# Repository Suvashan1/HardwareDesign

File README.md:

# STM32 Breakout-Board using STM32F103C8T6 Microcontroller

Using this medium-density microcontroller, an experimental peripheral board was designed using KiCAD to validate PCB design principles that I have learnt. It has formed a template for future layouts and schematic designs. For further information on my design choices, method and components selected and their placement, please read the design-considerations PDF in the file.

# Layout:

# Schematic:

# BOSCH BMP180 Drivers

The following device drivers were developed to be used with the respective breakout board designed, to test the I2C interface. All instructions and files can be found in the folder
added.

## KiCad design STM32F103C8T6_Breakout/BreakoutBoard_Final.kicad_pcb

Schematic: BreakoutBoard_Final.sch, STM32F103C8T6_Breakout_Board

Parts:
C1, C3: 12p; C_0805_2012Metric; LCSC Part # C1792
C2: 10u; C_1206_3216Metric; LCSC Part # C13585
C4: 10u; C_0805_2012Metric; LCSC Part # C15850
C5: 10u; C_0402_1005Metric; LCSC Part # C15525
C6, C8, C10, C11, C12, C13, C14, C16, C17, C18: 100n; C_0402_1005Metric; LCSC Part # C1525
C7, C9: 22p; C_0805_2012Metric; LCSC Part # C1804
C15: 1u; C_0603_1608Metric; LCSC Part # C15849
D1, D2: B5819W; D_SOD-123; LCSC Part # C8598
D3: Status; LED_0603_1608Metric; LCSC Part # C72041
J1: USB_B_Micro; USB_Micro-B_Molex-105017-0001
J2: SWD; PinHeader_2x05_P1.00mm_Vertical
J3: BMP180_I2C; PinSocket_1x04_P1.00mm_Vertical
J4: SPI_F; PinSocket_1x04_P1.00mm_Vertical
J5: USART_F; PinSocket_1x02_P1.00mm_Vertical
J6: SPI_M; PinHeader_1x04_P1.00mm_Vertical
J7: USART_M; PinHeader_1x02_P1.00mm_Vertical
J8: HC-05; PinSocket_1x04_P1.00mm_Vertical
J9: VCC_GND; PinHeader_1x02_P1.00mm_Vertical
J10: 3V3_GND; PinHeader_1x02_P1.00mm_Vertical
J11: 5V_GND; PinHeader_1x02_P1.00mm_Vertical
L1: Ferrite_Bead_Small; L_0805_2012Metric; LCSC Part # C1017
MH1, MH2, MH3, MH4: MountingHole_Pad; MountingHole_4.3mm_M4_Pad_Via
R1: 390; R_0805_2012Metric; LCSC Part # C17655
R2: 33ohm; R_0805_2012Metric; LCSC Part # C17634
R3, R4: 4.7k; R_1206_3216Metric; LCSC Part # C17936
R6, R8, R9, R10, R11: 1k; R_0402_1005Metric; LCSC Part # C11702
R7: 2.2k; R_0402_1005Metric; LCSC Part # C25879
R12: 1.5k; R_0201_0603Metric; LCSC Part # C22483
SW1: BOOT0_BOOT1; SW_DIP_SPSTx02_Slide_6.7x6.64mm_W7.62mm_P2.54mm_LowProfile
SW3: SW_Push_Dual; SW_PUSH_6mm
U1: USBLC6-2SC6; SOT-23-6; LCSC Part # C7519
U2: NCP1117; SOT-223-3_TabPin2; LCSC Part # C6186
U3: STM32F103C8Tx; LQFP-48_7x7mm_P0.5mm; LCSC Part # C8734
Y1: 16MHz; Crystal_SMD_3225-4Pin_3.2x2.5mm; LCSC Part # C13738
Y2: 32.768kHz; Crystal_SMD_3215-2Pin_3.2x1.5mm; LCSC Part # C32346

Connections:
+3.3VA: C14.1, C15.1, L1.1, U3.9
+3V3: C4.1, C5.1, C6.1, C8.1, C10.1, C11.1, C12.1, C16.1, C17.1, C18.1, J2.1, J3.4, J10.1, L1.2, R3.1, R4.1, R10.1, R11.1, R12.1, U2.2 (VO), U3.1, U3.24, U3.36, U3.48
+5V: D2.2, J1.1, J8.4, J11.1, U1.5
BOOT0: R8.1, SW1.1, U3.44
BOOT1: R9.1, SW1.2, U3.20
BT-RX: J8.1, R6.2, R7.2
BT-TX: J8.2, U3.22
GND: C1.2, C2.2, C3.2, C4.2, C5.2, C6.2, C7.2, C8.2, C9.2, C10.2, C11.2, C12.2, C13.1, C14.2, C15.2, C16.2, C17.2, C18.2, D3.1, J1.4, J1.5, J2.3, J2.5, J3.3, J8.3, J9.2, J10.2, J11.2, MH1.1, MH2.1, MH3.1, MH4.1, R7.1, R8.2, R9.2, SW3.2, U1.2, U2.1 (GND), U3.8, U3.23, U3.35, U3.47, Y1.2, Y1.4
HSE_IN: C1.1, U3.5, Y1.1
HSE_OUT: R1.1, U3.6
I2C_SCL: J3.2, R4.2, U3.42
I2C_SDA: J3.1, R3.2, U3.43
LSE_IN: C7.1, U3.3, Y2.1
LSE_OUT: C9.1, U3.4, Y2.2
NRST: C13.2, J2.10, SW3.1, U3.7
unnamed: C2.1, D1.1, D2.1, U2.3 (VI)
unnamed: C3.1, R1.2, Y1.3
unnamed: D3.2, R2.1
unnamed: R2.2, U3.18
unnamed: R10.2, SW1.4
unnamed: R11.2, SW1.3
SPI_MISO: J4.3, J6.2, U3.16
SPI_MOSI: J4.4, J6.1, U3.17
SPI_NSS: J4.1, J6.4, U3.14
SPI_SCK: J4.2, J6.3, U3.15
SWD_IO: J2.2, U3.34
SWO: J2.6, U3.39
SW_CLK: J2.4, U3.37
USART1_RX: J5.2, J7.2, U3.31
USART1_TX: J5.1, J7.1, U3.30
USART3_TX: R6.1, U3.21
USB_+: U1.4, U3.33
USB_-: U1.6, U3.32
USB_CONN+: J1.3, U1.3
USB_CONN-: J1.2, U1.1
USB_DP: R12.2
VCC: D1.2, J9.1

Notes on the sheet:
Power supply and filtering
CL = 2 * (Cr - Cparasitic) = 12pF Cr = 9pF
HSE
USB
Connectors
MCU
CL = 2 * (Cr - Cparasitic) = 22p Cr = 12.5p
LSE

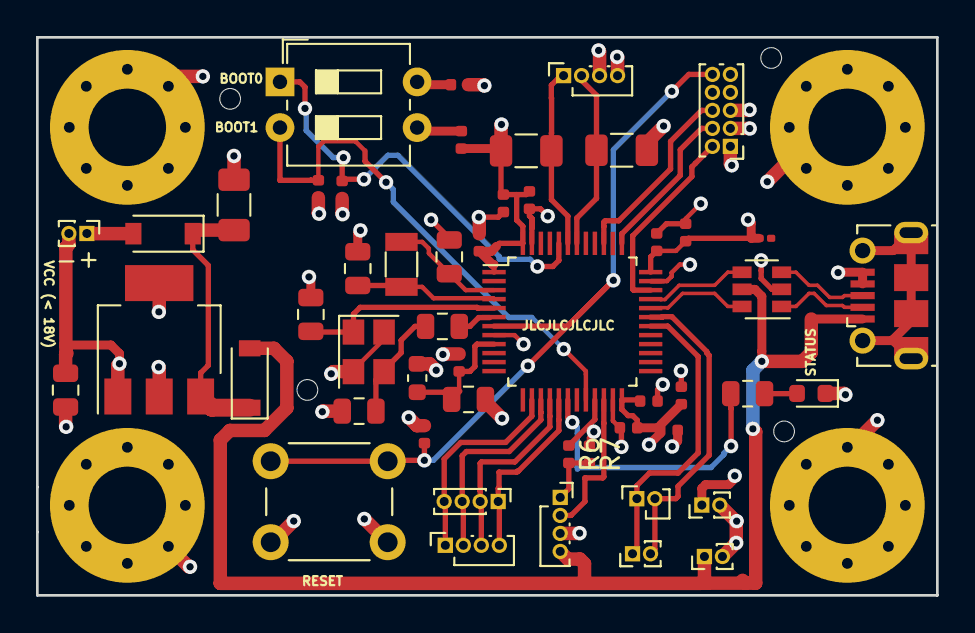
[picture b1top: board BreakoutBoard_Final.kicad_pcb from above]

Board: 4 copper layers, 50.0 x 31.0 mm, 55 parts (0 on the bottom side), 36 nets.

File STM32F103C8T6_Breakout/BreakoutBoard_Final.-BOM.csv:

Reference, Quantity, Value, Footprint, Datasheet, LCSC Part #
C15 ,1,"1u","Capacitor_SMD:C_0603_1608Metric","~","C15849"
C2 ,1,"10u","Capacitor_SMD:C_1206_3216Metric","~","C13585"
C1 C3 ,2,"12p","Capacitor_SMD:C_0805_2012Metric","~","C1792"
C4 ,1,"10u","Capacitor_SMD:C_0805_2012Metric","~","C15850"
C5 ,1,"10u","Capacitor_SMD:C_0402_1005Metric","~","C15525"
C10 C11 C12 C13 C14 C16 C17 C18 C6 C8 ,10,"100n","Capacitor_SMD:C_0402_1005Metric","~","C1525"
C7 C9 ,2,"22p","Capacitor_SMD:C_0805_2012Metric","~","C1804"
D1 D2 ,2,"B5819W","Diode_SMD:D_SOD-123","~","C8598"
D3 ,1,"Status","LED_SMD:LED_0603_1608Metric","~","C72041"
J1 ,1,"USB_B_Micro","Connector_USB:USB_Micro-B_Molex-105017-0001","~"
J10 ,1,"3V3_GND","Connector_PinHeader_1.00mm:PinHeader_1x02_P1.00mm_Vertical","~"
J11 ,1,"5V_GND","Connector_PinHeader_1.00mm:PinHeader_1x02_P1.00mm_Vertical","~"
J2 ,1,"SWD","Connector_PinHeader_1.00mm:PinHeader_2x05_P1.00mm_Vertical","~"
J3 ,1,"BMP180_I2C","Connector_PinSocket_1.00mm:PinSocket_1x04_P1.00mm_Vertical","~"
J4 ,1,"SPI_F","Connector_PinSocket_1.00mm:PinSocket_1x04_P1.00mm_Vertical","~"
J5 ,1,"USART_F","Connector_PinSocket_1.00mm:PinSocket_1x02_P1.00mm_Vertical","~"
J6 ,1,"SPI_M","Connector_PinHeader_1.00mm:PinHeader_1x04_P1.00mm_Vertical","~"
J7 ,1,"USART_M","Connector_PinHeader_1.00mm:PinHeader_1x02_P1.00mm_Vertical","~"
J8 ,1,"HC-05 ","Connector_PinSocket_1.00mm:PinSocket_1x04_P1.00mm_Vertical","~"
J9 ,1,"VCC_GND","Connector_PinHeader_1.00mm:PinHeader_1x02_P1.00mm_Vertical","~"
L1 ,1,"Ferrite_Bead_Small","Inductor_SMD:L_0805_2012Metric","~","C1017"
MH1 MH2 MH3 MH4 ,4,"MountingHole_Pad","MountingHole:MountingHole_4.3mm_M4_Pad_Via","~"
R1 ,1,"390","Resistor_SMD:R_0805_2012Metric","~","C17655"
R12 ,1,"1.5k","Resistor_SMD:R_0201_0603Metric","~","C22483"
R2 ,1,"33ohm","Resistor_SMD:R_0805_2012Metric","~","C17634"
R3 R4 ,2,"4.7k","Resistor_SMD:R_1206_3216Metric","~","C17936"
R10 R11 R6 R8 R9 ,5,"1k","Resistor_SMD:R_0402_1005Metric","~","C11702"
R7 ,1,"2.2k","Resistor_SMD:R_0402_1005Metric","~","C25879"
SW1 ,1,"BOOT0_BOOT1","Button_Switch_THT:SW_DIP_SPSTx02_Slide_6.7x6.64mm_W7.62mm_P2.54mm_LowProfile",""
SW3 ,1,"SW_Push_Dual","Button_Switch_THT:SW_PUSH_6mm",""
U1 ,1,"USBLC6-2SC6","Package_TO_SOT_SMD:SOT-23-6","http://www2.st.com/resource/en/datasheet/CD00050750.pdf","C7519"
U2 ,1,"NCP1117","Package_TO_SOT_SMD:SOT-223-3_TabPin2","http://www.onsemi.com/pub_link/Collateral/NCP1117-D.PDF","C6186"
U3 ,1,"STM32F103C8Tx","Package_QFP:LQFP-48_7x7mm_P0.5mm","http://www.st.com/st-web-ui/static/active/en/resource/techni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","C8734"
Y1 ,1,"16MHz","Crystal:Crystal_SMD_3225-4Pin_3.2x2.5mm","~","C13738"
Y2 ,1,"32.768kHz","Crystal:Crystal_SMD_3215-2Pin_3.2x1.5mm","~","C32346"

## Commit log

2020-10-18 Initial commit
    Initial PCB design of STM32F103C8T6 breakout board
2020-10-18 Hardware Design Summary
2021-01-18 BOSCH BMP180 Device drivers added
